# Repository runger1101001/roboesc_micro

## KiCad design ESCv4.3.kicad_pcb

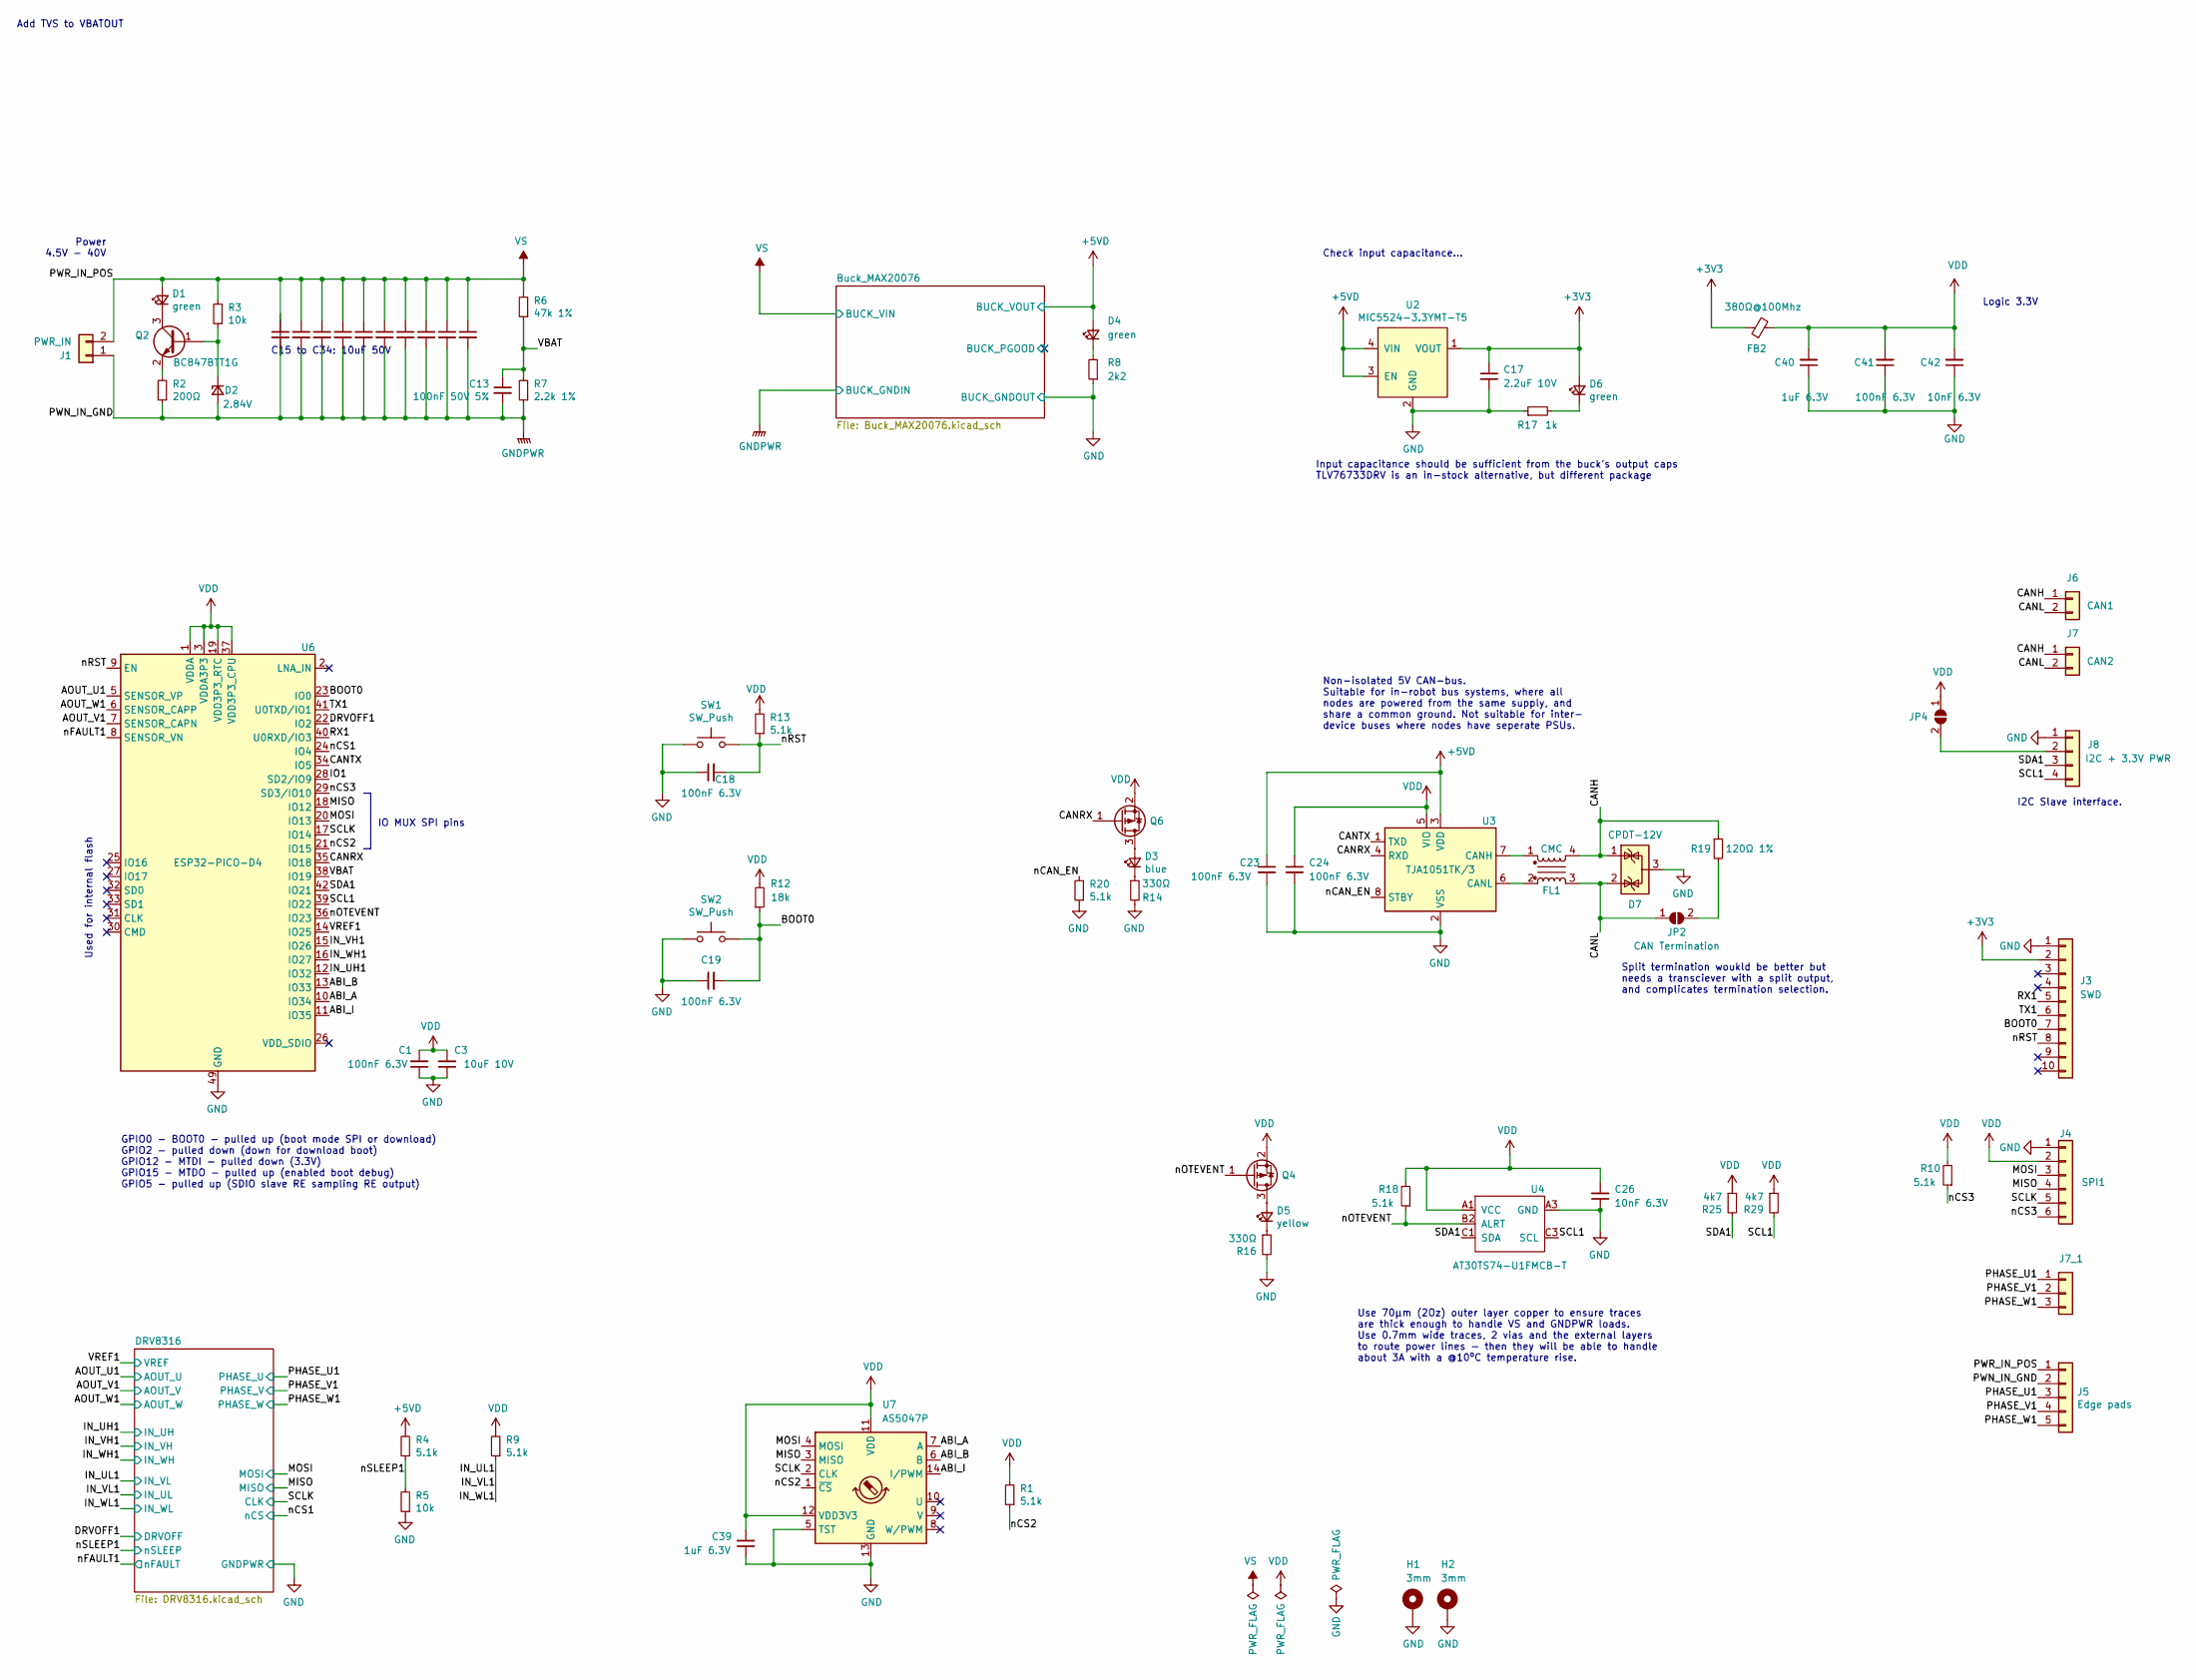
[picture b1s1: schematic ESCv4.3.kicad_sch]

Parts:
C1, C18, C19, C41: 100nF 6.3V; C_0402_1005Metric; Part CL05B104KQ5NNNC
C2, C4, C5, C6, C7, C8, C9, C10, C11, C12: 10uF 50V; C_0805_2012Metric; Part GRM21BR61H106KE43L
C3: 10uF 10V; C_0402_1005Metric; Part ZRB15XR61A106ME01D
C13: 100nF 50V 5%; C_0402_1005Metric; Part GRM155C71H104JE19D
C17: 2.2uF 10V; C_0603_1608Metric; Part GRM188R71A225KE15D
C23, C24: 100nF 6.3V; C_0402_1005Metric
C26, C42: 10nF 6.3V; C_0402_1005Metric; Part CC0402KRX7R5BB103
C39, C40: 1uF 6.3V; C_0402_1005Metric; Part GRT155C80J105KE01D
D1, D4, D6: green; LED_0402_1005Metric; Part SML-P12MTT86
D2: 2.84V; D_SOD-523; Part CZRU52C2V7-HF
D3: blue; LED_0402_1005Metric; Part LB QH9G-N1OO-35-1
D5: yellow; LED_0402_1005Metric; Part SML-P12YTT86RR
D7: CPDT-12V; SOT-23; Part CPDT-12V
FB2: 380Ω@100Mhz; L_0603_1608Metric; Part BLM18DN381SH1D
FL1: CMC; CMC_Filter_0504; Part KCZ1210AH900HRTD25
H1, H2: 3mm; MountingHole_2.2mm_M2_Pad_Via
J1: PWR_IN; AMASS_XT30UPB-M_1x02_P5.0mm_Vertical
J3: Conn_01x10; SAMTEC_SEI-110_Mating
J4: SPI1; JST_SH_BM06B-SRSS-TB_1x06-1MP_P1.00mm_Vertical; Part JST_SH_BM06B-SRSS-TB_1x06-1MP
J5: Conn_01x05; Motor_Power_Pads_CircleEdge40mm
J6: CAN1; JST_PH_B2B-PH-K_1x02_P2.00mm_Vertical; Part JST_PH_B2B-PH-K_1x02_P2.00mm_Vertical
J7: CAN2; JST_PH_B2B-PH-K_1x02_P2.00mm_Vertical; Part JST_PH_B2B-PH-K_1x02_P2.00mm_Vertical
J7_1: Phase_Pads; PinHeader_1x03_P2.54mm_Vertical
J8: Conn_01x04; JST_SH_BM04B-SRSS-TB_1x04-1MP_P1.00mm_Vertical; Part JST_SH_BM04B-SRSS-TB_1x04-1MP
JP2: CAN Termination; SolderJumper-2_P1.3mm_Open_TrianglePad1.0x1.5mm
JP4: SolderJumper_2_Open; SolderJumper-2_P1.3mm_Open_TrianglePad1.0x1.5mm
Q2: BC847BTT1G; SOT-416; Part BC847BTT1G
Q4, Q6: CSD25501F3; FemtoFET_0.7x0.6_YJN3; Part CSD25501F3
R1, R4, R9, R10, R13, R18, R20: 5.1k; R_0402_1005Metric
R2: 200Ω; R_0402_1005Metric
R3, R5: 10k; R_0402_1005Metric
R6: 47k 1%; R_0402_1005Metric
R7: 2.2k 1%; R_0402_1005Metric
R8: 2k2; R_0402_1005Metric
R12: 18k; R_0402_1005Metric
R14, R16: 330Ω; R_0402_1005Metric
R17: 1k; R_0402_1005Metric
R19: 120Ω 1%; R_0402_1005Metric
R25, R29: 4k7; R_0402_1005Metric
SW1: SW_Push; NANOT240; Part USLPT2616CT2TR
SW2: SW_Push; NANOT240; Part NANOT240
U2: MIC5524-3.3YMT-T5; TDFN-4-1EP_1x1mm_P0.65mm_EP0.5x0.5mm; Part MIC5524-3.3YMT-T5
U3: TJA1051TK/3; DFN-8-1EP_3x3mm_P0.65mm_EP1.55x2.4mm; Part TJA1051TK/3
U4: AT30TS74-U1FMCB-T; Texas_DSBGA-5_0.822x1.116mm_Layout2x1x2_P0.4mm; Part AT30TS74-U1FMCB-T
U6: ESP32-PICO-D4; QFN-48-1EP_7x7mm_P0.5mm_EP5.3x5.3mm; Part ESP32-PICO-D4
U7: AS5047P; TSSOP-14_4.4x5mm_P0.65mm; Part AS5047P

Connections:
+3V3: C17.1, D6.2 (A), FB2.1, J3.2, U2.1 (VOUT); also elsewhere on the board
+5VD: C23.1, D4.2 (A), R4.2, U2.3 (EN), U2.4 (VIN), U3.3 (VDD); also elsewhere on the board
/ABI_A: U6.10 (IO34), U7.7 (A)
/ABI_B: U6.13 (IO33), U7.6 (B)
/ABI_I: U6.11 (IO35), U7.14 (I/PWM)
/AOUT_U1: U6.5 (SENSOR_VP); also elsewhere on the board
/AOUT_V1: U6.7 (SENSOR_CAPN); also elsewhere on the board
/AOUT_W1: U6.6 (SENSOR_CAPP); also elsewhere on the board
/BOOT0: C19.2, J3.7, R12.1, SW2.2, U6.23 (IO0); also elsewhere on the board
/CANH: D7.1 (K), FL1.4, J6.1, J7.1, R19.1
/CANL: D7.2 (K), FL1.3, J6.2, J7.2, JP2.1 (A)
/CANRX: Q6.1 (G), U3.4 (RXD), U6.35 (IO18)
/CANTX: U3.1 (TXD), U6.34 (IO5)
/DRVOFF1: U6.22 (IO2); also elsewhere on the board
/IN_UH1: U6.12 (IO32); also elsewhere on the board
/IN_UL1: R9.1; also elsewhere on the board
/IN_VH1: U6.15 (IO26); also elsewhere on the board
/IN_WH1: U6.16 (IO27); also elsewhere on the board
/IO1: U6.28 (SD2/IO9)
/MISO: J4.4, U6.18 (IO12), U7.3 (MISO); also elsewhere on the board
/MOSI: J4.3, U6.20 (IO13), U7.4 (MOSI); also elsewhere on the board
/PHASE_U1: J5.3, J7_1.1; also elsewhere on the board
/PHASE_V1: J5.4, J7_1.2; also elsewhere on the board
/PHASE_W1: J5.5, J7_1.3; also elsewhere on the board
/RX1: J3.5, U6.40 (U0RXD/IO3); also elsewhere on the board
/SCL1: J8.4, R29.2, U4.C3 (SCL), U6.39 (IO22)
/SCLK: J4.5, U6.17 (IO14), U7.2 (CLK); also elsewhere on the board
/SDA1: J8.3, R25.2, U4.C1 (SDA), U6.42 (IO21)
/TX1: J3.6, U6.41 (U0TXD/IO1); also elsewhere on the board
/VBAT: C13.1, R6.1, R7.2, U6.38 (IO19)
/VREF1: U6.14 (IO25); also elsewhere on the board
/nCAN_EN: R20.2, U3.8 (STBY)
/nCS1: U6.24 (IO4); also elsewhere on the board
/nCS2: R1.1, U6.21 (IO15), U7.1 (~CS)
/nCS3: J4.6, R10.1, U6.29 (SD3/IO10)
/nFAULT1: U6.8 (SENSOR_VN); also elsewhere on the board
/nOTEVENT: Q4.1 (G), R18.1, U4.B2 (ALRT), U6.36 (IO23)
/nRST: C18.2, J3.8, R13.1, SW1.2, U6.9 (EN); also elsewhere on the board
/nSLEEP1: R4.1, R5.2; also elsewhere on the board
unnamed: D1.1 (K), Q2.3 (C)
unnamed: D2.1 (K), Q2.1 (B), R3.1
unnamed: D3.1 (K), R14.1
unnamed: D3.2 (A), Q6.3 (D)
unnamed: D4.1 (K), R8.2
unnamed: D5.1 (K), R16.1
unnamed: D5.2 (A), Q4.3 (D)
unnamed: D6.1 (K), R17.2
unnamed: FL1.1, U3.7 (CANH)
unnamed: FL1.2, U3.6 (CANL)
unnamed: J8.2, JP4.2 (B)
unnamed: JP2.2 (B), R19.2
unnamed: Q2.2 (E), R2.2
VS: C2.1, C4.1, C5.1, C6.1, C7.1, C8.1, C9.1, C10.1, C11.1, C12.1, D1.2 (A), J1.2, J5.1, R3.2, R6.2; also elsewhere on the board

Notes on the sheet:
Add TVS to VBATOUT
IO MUX SPI pins
Input capacitance should be sufficient from the buck’s output caps TLV76733DRV is an in-stock alternative, but different package
I2C Slave interface.
GPIO0 - BOOT0 - pulled up (boot mode SPI or download) GPIO2 - pulled down (down for download boot) GPIO12 - MTDI - pulled down (3.3V) GPIO15 - MTDO - pulled up (enabled boot debug) GPIO5 - pulled up (SDIO slave RE sampling RE output)
C15 to C34: 10uF 50V
Power 4.5V - 40V
Used for internal flash
Logic 3.3V
Check input capacitance…
Non-isolated 5V CAN-bus. Suitable for in-robot bus systems, where all nodes are powered from the same supply, and share a common ground. Not suitable for inter- device buses where nodes have seperate PSUs.
Split termination woukld be better but needs a transciever with a split output, and complicates termination selection.
Use 70µm (2Oz) outer layer copper to ensure traces are thick enough to handle VS and GNDPWR loads. Use 0.7mm wide traces, 2 vias and the external layers to route power lines - then they will be able to handle about 3A with a @10ºC temperature rise.

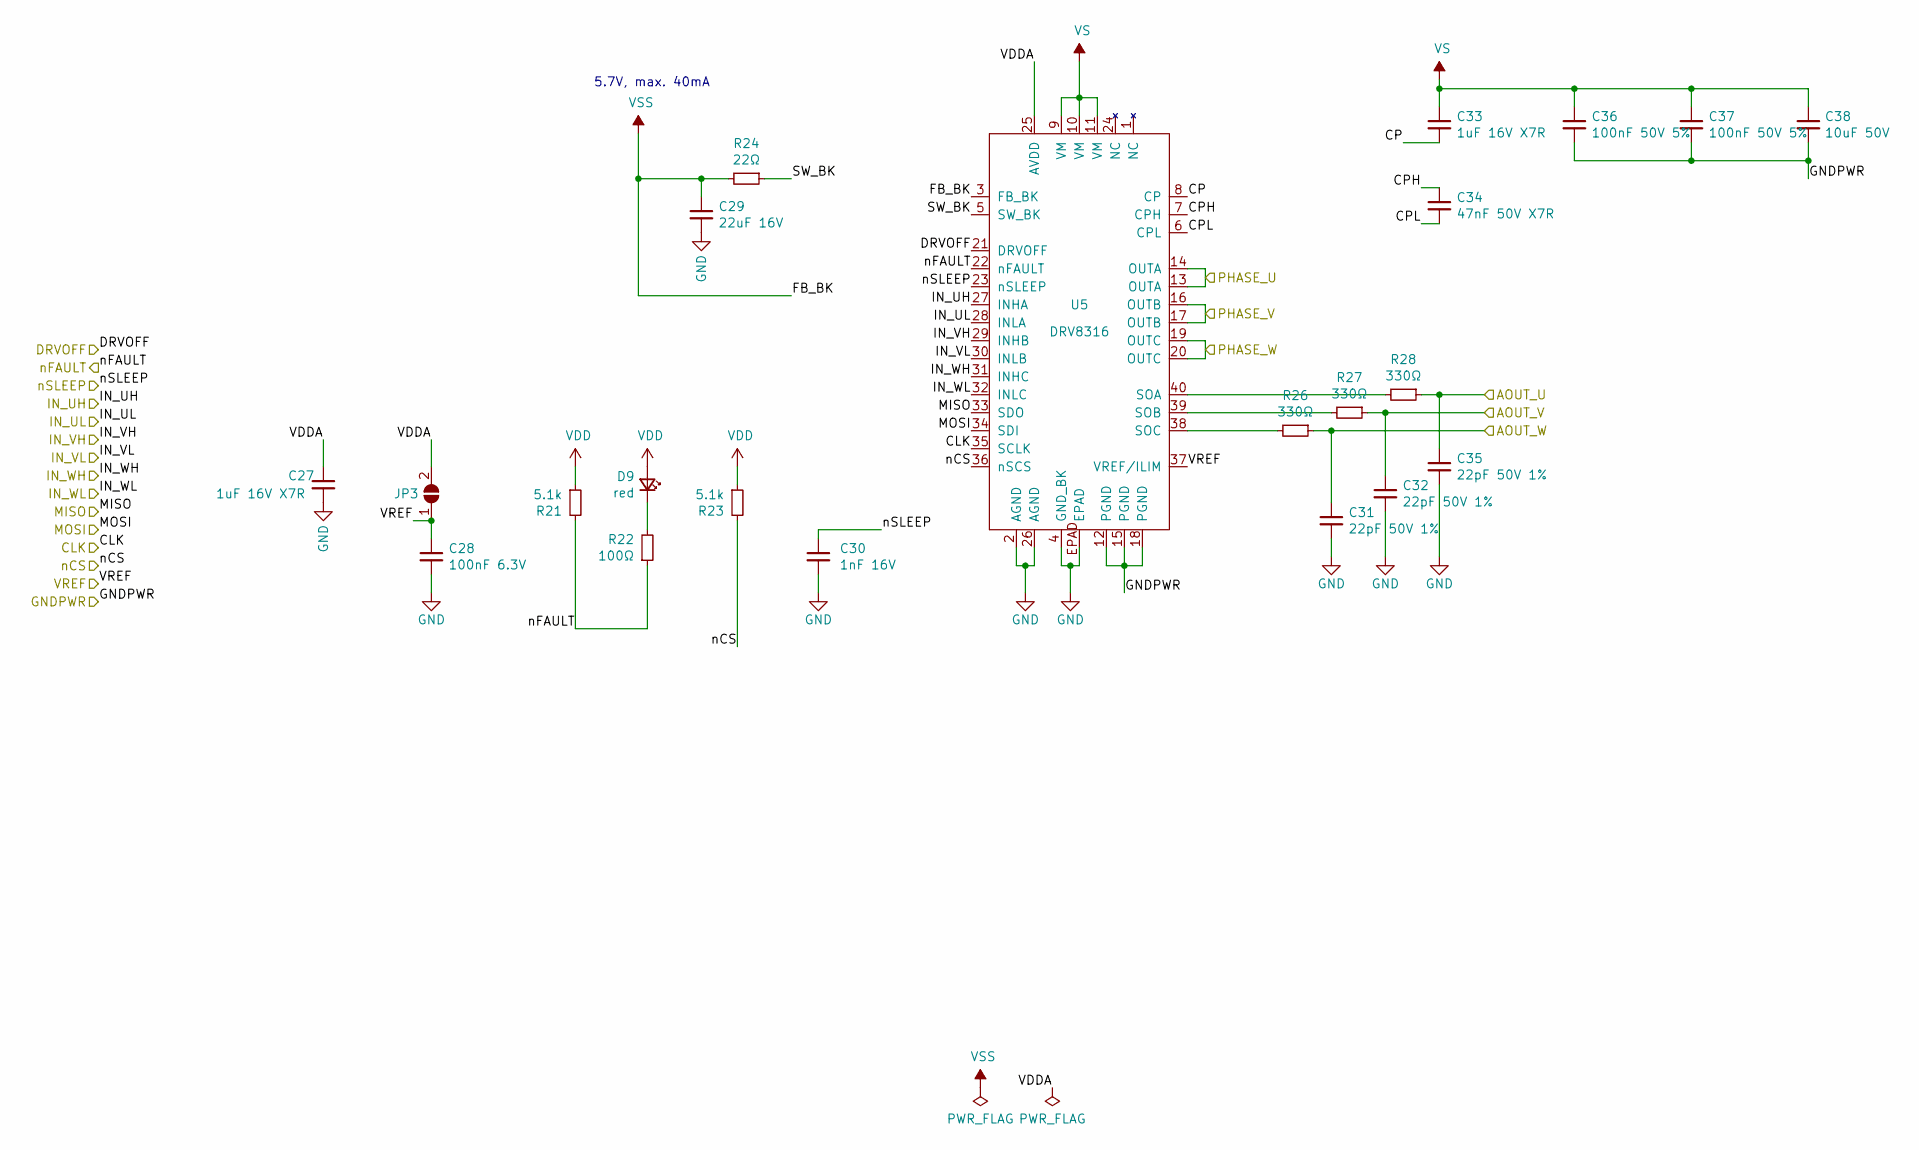
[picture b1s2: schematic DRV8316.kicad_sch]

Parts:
C27: 1uF 16V X7R; C_0402_1005Metric; Part 0603YC105JAT2A
C28: 100nF 6.3V; C_0402_1005Metric; Part CL05B104KQ5NNNC
C29: 22uF 16V; C_0805_2012Metric; Part GRM219R61C226ME15L
C30: 1nF 16V; C_0402_1005Metric; Part 0402YC102KAT2A
C31, C32, C35: 22pF 50V 1%; C_0402_1005Metric; Part GRM1555C1H220FA01D
C33: 1uF 16V X7R; C_0603_1608Metric; Part 0603YC105JAT2A
C34: 47nF 50V X7R; C_0402_1005Metric; Part GRM155R71H473KE14D
C36, C37: 100nF 50V 5%; C_0402_1005Metric; Part GRM155C71H104JE19D
C38: 10uF 50V; C_0805_2012Metric; Part GRM21BR61H106KE43L
D9: red; LED_0402_1005Metric; Part 150040RS73240
JP3: VSS2VDD; SolderJumper-2_P1.3mm_Open_TrianglePad1.0x1.5mm
R21, R23: 5.1k; R_0402_1005Metric
R22: 100Ω; R_0402_1005Metric
R24: 22Ω; R_0402_1005Metric
R26, R27, R28: 330Ω; R_0402_1005Metric
U5: DRV8316; vQFN-40_EP_5x7_Pitch0.5mm; Part DRV8316

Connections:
/AOUT_U1: C35.1, R28.1; also elsewhere on the board
/AOUT_V1: C32.1, R27.1; also elsewhere on the board
/AOUT_W1: C31.1, R26.1; also elsewhere on the board
/DRV8316/CP: C33.2, U5.8 (CP)
/DRV8316/CPH: C34.1, U5.7 (CPH)
/DRV8316/CPL: C34.2, U5.6 (CPL)
/DRV8316/SW_BK: R24.1, U5.5 (SW_BK)
/DRV8316/VDDA: C27.1, JP3.2 (B), U5.25 (AVDD)
/DRVOFF1: U5.21 (DRVOFF); also elsewhere on the board
/IN_UH1: U5.27 (INHA); also elsewhere on the board
/IN_UL1: U5.28 (INLA), U5.30 (INLB), U5.32 (INLC); also elsewhere on the board
/IN_VH1: U5.29 (INHB); also elsewhere on the board
/IN_WH1: U5.31 (INHC); also elsewhere on the board
/MISO: U5.33 (SDO); also elsewhere on the board
/MOSI: U5.34 (SDI); also elsewhere on the board
/PHASE_U1: U5.13 (OUTA), U5.14 (OUTA); also elsewhere on the board
/PHASE_V1: U5.16 (OUTB), U5.17 (OUTB); also elsewhere on the board
/PHASE_W1: U5.19 (OUTC), U5.20 (OUTC); also elsewhere on the board
/SCLK: U5.35 (SCLK); also elsewhere on the board
/VREF1: C28.1, JP3.1 (A), U5.37 (VREF/ILIM); also elsewhere on the board
/nCS1: R23.2, U5.36 (nSCS); also elsewhere on the board
/nFAULT1: R21.2, R22.1, U5.22 (nFAULT); also elsewhere on the board
/nSLEEP1: C30.1, U5.23 (nSLEEP); also elsewhere on the board
unnamed: D9.1 (K), R22.2
unnamed: R26.2, U5.38 (SOC)
unnamed: R27.2, U5.39 (SOB)
unnamed: R28.2, U5.40 (SOA)
VS: C33.1, C36.1, C37.1, C38.1, U5.9 (VM), U5.10 (VM), U5.11 (VM); also elsewhere on the board
VSS: C29.1, R24.2, U5.3 (FB_BK)

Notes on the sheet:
5.7V, max. 40mA

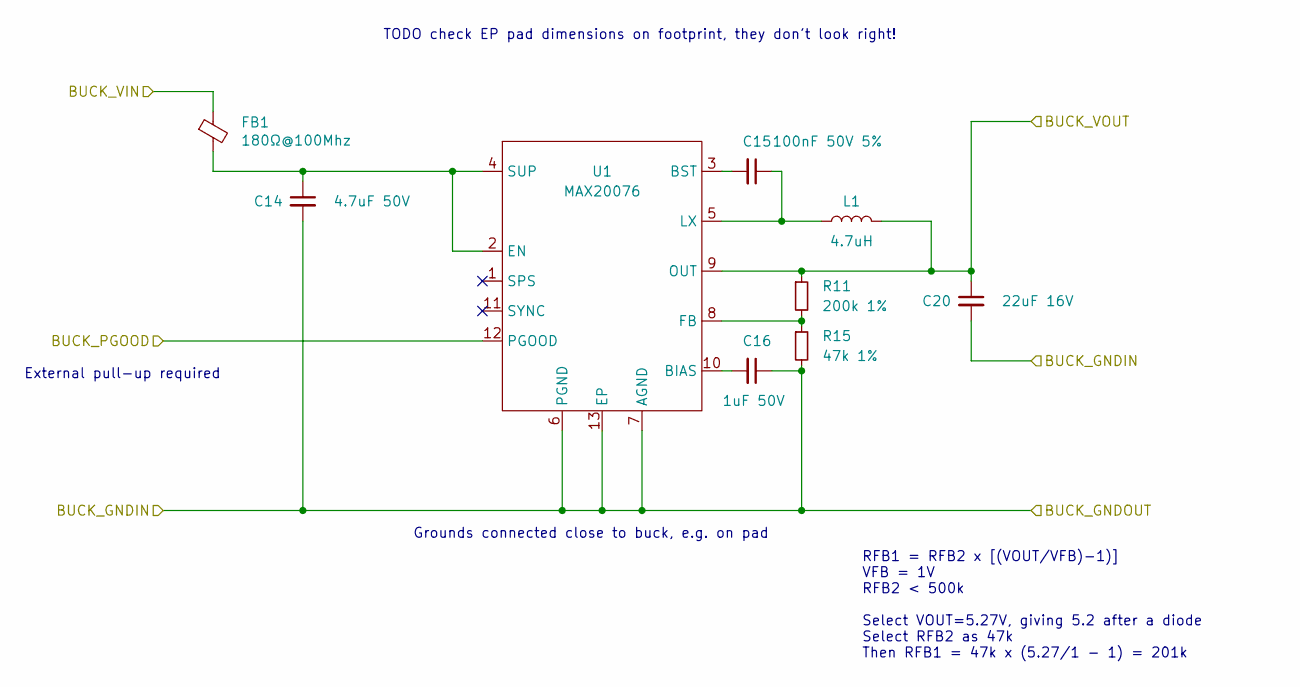
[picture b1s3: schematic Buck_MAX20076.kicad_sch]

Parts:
C14: 4.7uF 50V; C_0805_2012Metric; Part GRM21BZ71H475ME15K
C15: 100nF 50V 5%; C_0402_1005Metric; Part GRM155C71H104JE19D
C16: 1uF 50V; C_0402_1005Metric; Part GRM155R61H105KE05D
C20: 22uF 16V; C_0603_1608Metric; Part CL10A226MO7JZNC
FB1: 180Ω@100Mhz; L_0805_2012Metric; Part BLM21SP181SZ1D
L1: 4.7uH; L_Coilcraft_XxL4030; Part XAL4030-472MEC
R11: 200k 1%; R_0402_1005Metric; Part ERJ2RKD2003X
R15: 47k 1%; R_0402_1005Metric; Part TNPW040247K0BYEP
U1: MAX20076; DFN-12-1EP_3x3mm_P0.5mm_EP1.7x2.5mm; Part MAX20076EATCB/VY+

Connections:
+5VD: C20.1, L1.2, R11.1, U1.9 (OUT); also elsewhere on the board
/Buck_MAX20076/BUCK_PGOOD: U1.12 (PGOOD)
unnamed: C14.1, FB1.2, U1.2 (EN), U1.4 (SUP)
unnamed: C15.1, L1.1, U1.5 (LX)
unnamed: C15.2, U1.3 (BST)
unnamed: C16.2, U1.10 (BIAS)
unnamed: R11.2, R15.1, U1.8 (FB)
VS: FB1.1; also elsewhere on the board

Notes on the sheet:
TODO check EP pad dimensions on footprint, they don't look right!
Grounds connected close to buck, e.g. on pad
RFB1 = RFB2 x [(VOUT/VFB)-1)] VFB = 1V RFB2 < 500k Select VOUT=5.27V, giving 5.2 after a diode Select RFB2 as 47k Then RFB1 = 47k x (5.27/1 - 1) = 201k
External pull-up required

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
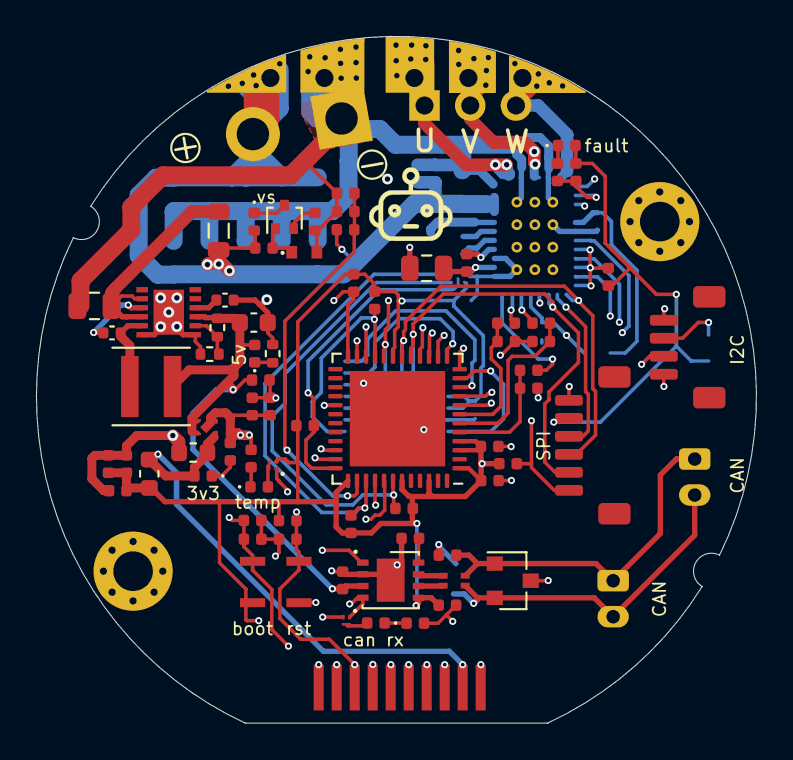
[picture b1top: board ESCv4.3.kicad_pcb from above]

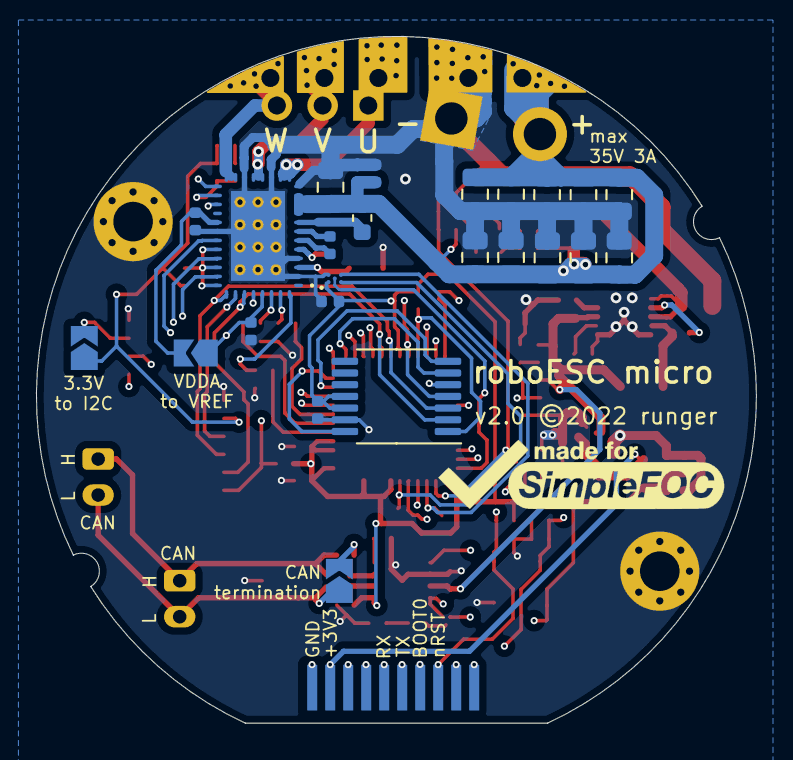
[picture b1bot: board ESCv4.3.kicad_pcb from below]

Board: 4 copper layers, 40.0 x 38.1 mm, 106 parts (26 on the bottom side), 69 nets.

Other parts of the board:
J3#2: Conn_01x10; SAMTEC_SEI-110_Mating

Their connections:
+3V3: J3#2.2; also elsewhere on the board
/BOOT0: J3#2.7; also elsewhere on the board
/RX1: J3#2.5; also elsewhere on the board
/TX1: J3#2.6; also elsewhere on the board
/nRST: J3#2.8; also elsewhere on the board

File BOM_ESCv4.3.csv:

Item,Ref Des,Qty,Manufacturer,Mfg Part #,Description / Value,Package,Type,Your Instructions / Notes
1,"C13,C16,C36,C37",4,Murata,GRM155C71H104JE19D,100nF 50V 5%,C_0402_1005Metric,SMD,GRM155C71H104JE19D or similar; Unpolarized capacitor;
2,C17,1,Murata,GRM188R71A225KE15D,2.2uF 10V,C_0603_1608Metric,SMD,; Unpolarized capacitor; 
3,"C18,C19,C23,C24,C41,C1,C28",7,Samsung,CL05B104KQ5NNNC,100nF 6.3V,C_0402_1005Metric,SMD,CL05B104KQ5NNNC or similar; Unpolarized capacitor;
4,"C21,C20,C22,C29",4,Murata,GRM219R61C226ME15L,22uF 16V,C_0805_2012Metric,SMD,; Unpolarized capacitor; 
5,"C26,C42",2,Yageo,CC0402KRX7R5BB103,10nF 6.3V,C_0402_1005Metric,SMD,Any 10nF 6.3V X5R or X7R ceramic capacitor; Unpolarized capacitor;
6,C3,1,Murata,ZRB15XR61A106ME01D,10uF 10V,C_0402_1005Metric,SMD,; Unpolarized capacitor; 
7,C30,1,AVX,0402YC102KAT2A,1nF 16V,C_0402_1005Metric,SMD,0402YC102KAT2A or similar 1nF 16V; Unpolarized capacitor;
8,"C31,C32,C35",3,Murata,GRM1555C1H220FA01D,22pF 50V 1%,C_0402_1005Metric,SMD,GRM1555C1H220FA01D - 50V.    ; Unpolarized capacitor;
9,"C33,C27",2,AVX,0603YC105JAT2A,1uF 16V X7R,C_0402_1005Metric,SMD,6.3V would be enough; Unpolarized capacitor;
10,C34,1,Murata,GRM155R71H473KE14D,47nF 50V X7R,C_0402_1005Metric,SMD,; Unpolarized capacitor; 
11,"C39,C40",2,Murata,GRT155C80J105KE01D,1uF 6.3V,C_0402_1005Metric,SMD,; Unpolarized capacitor; 
12,"C4,C2,C6,C5,C7,C9,C8,C10,C12,C11,C14,C15,C38",13,Murata,GRM21BR61H106KE43L,10uF 50V,C_0805_2012Metric,SMD,; Unpolarized capacitor; 
13,"D1,D4,D6",3,ROHM,SML-P12MTT86,green,LED_0402_1005Metric,SMD,; Light emitting diode; 
14,D2,1,Comchip,CZRU52C2V7-HF,2.84V,D_SOD-523,SMD,Any 2.84V (+/-0.2V) Zener diode; Zener diode; https://www.mouser.at/datasheet/2/80/CZRU52C2-HF_THRU_CZRU52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
15,D3,1,OSRAM Opto,LB QH9G-N1OO-35-1,blue,LED_0402_1005Metric,SMD,; Light emitting diode; 
16,D5,1,ROHM Semiconductors,SML-P12YTT86RR,yellow,LED_0402_1005Metric,SMD,; Light emitting diode; 
17,D7,1,Comchip,CPDT-12V,CPDT-12V,SOT-23,SMD,"; Dual Line CAN Bus Protector, 24Vrwm; http://www.onsemi.com/pub_link/Collateral/NUP2105L-D.PDF"
18,D9,1,Wurth,150040RS73240,red,LED_0402_1005Metric,SMD,any approx. 2V red LED; Light emitting diode; https://www.mouser.at/datasheet/2/445/150040RS73240-1713960.pdf
19,FB1,1,Murata,BLM21SP181SZ1D,180Ω@100Mhz,L_0805_2012Metric,SMD,; Ferrite bead; 
20,FB2,1,Murata,BLM18DN381SH1D,380Ω@100Mhz,L_0603_1608Metric,SMD,; Ferrite bead; 
21,FL1,1,TDK,KCZ1210AH900HRTD25,CMC,CMC_Filter_0504,SMD,"; EMI 2-inductor filter, pin-connections 1-4 and 2-3;"
25,J4,1,JST,JST_SH_BM06B-SRSS-TB_1x06-1MP,SPI1,JST_SH_BM06B-SRSS-TB_1x06-1MP_P1.00mm_Vertical,SMD,"; Generic connector, single row, 01x06, script generated (kicad-library-utils/schlib/autogen/connector/);"
30,J8,1,JST,JST_SH_BM04B-SRSS-TB_1x04-1MP,Conn_01x04,JST_SH_BM04B-SRSS-TB_1x04-1MP_P1.00mm_Vertical,SMD,"; Generic connector, single row, 01x04, script generated (kicad-library-utils/schlib/autogen/connector/);"
34,L1,1,Coilcraft,XGL4020-102MEC,1uH,L_Coilcraft_XxL4020,SMD,; Inductor; 
35,Q2,1,On Semi,BC847BTT1G,BC847BTT1G,SOT-416,SMD,"beta=150 footprint SC-75-3; NPN transistor, base/emitter/collector;"
36,"Q4,Q6",2,TI,CSD25501F3,CSD25501F3,FemtoFET_0.7x0.6_YJN3,SMD,"; P-MOSFET transistor, gate/source/drain; "
37,R11,1,,Resistor,1MΩ,R_0402_1005Metric,SMD,; Resistor; 
38,R12,1,,Resistor,18k,R_0402_1005Metric,SMD,; Resistor; 
39,R15,1,,Resistor,2k2,R_0402_1005Metric,SMD,; Resistor; 
40,"R16,R14,R28,R27,R26",5,,Resistor,330Ω,R_0402_1005Metric,SMD,; Resistor; 
41,R17,1,,Resistor,1k,R_0402_1005Metric,SMD,; Resistor; 
42,R19,1,,Resistor,120Ω 1%,R_0402_1005Metric,SMD,; Resistor; 
43,R2,1,,Resistor,200Ω,R_0402_1005Metric,SMD,; Resistor; 
44,R22,1,,Resistor,100Ω,R_0402_1005Metric,SMD,; Resistor; 
45,R24,1,,Resistor,22Ω,R_0402_1005Metric,SMD,; Resistor; 
46,"R25,R29",2,,Resistor,4k7,R_0402_1005Metric,SMD,; Resistor; 
47,"R3,R5",2,,Resistor,10k,R_0402_1005Metric,SMD,; Resistor; 
48,"R4,R13,R18,R20,R9,R1,R10,R21,R23",9,,Resistor,5.1k,R_0402_1005Metric,SMD,; Resistor; 
49,R6,1,,Resistor,47k 1%,R_0402_1005Metric,SMD,; Resistor; 
50,R7,1,,Resistor,2.2k 1%,R_0402_1005Metric,SMD,; Resistor; 
51,"SW1,SW2",2,TE Connectivity / Alcoswitch,USLPT2616CT2TR,SW_Push,USLPT2616CT2TR,SMD,"; Push button switch, generic, two pins; "
52,U1,1,TI,TPS63061,TPS63061,Texas_S-PWSON-N10_ThermalVias,SMD,"; Buck/boost regulator 1.3A boost, 2A buck, 5V fixed output voltage; http://www.ti.com/lit/ds/symlink/tps63060.pdf"
53,U2,1,Micrel / Microchip,MIC5524-3.3YMT-T5,MIC5524-3.3YMT-T5,TDFN-4-1EP_1x1mm_P0.65mm_EP0.5x0.5mm,SMD,"; 500mA low dropout LDO, Fixed or Adjustable, 1x1mm Thin-DFN; https://www.mouser.at/datasheet/2/268/MIC5524-875860.pdf"
54,U3,1,Microchip,MCP2542WFDxMF,MCP2542WFDxMF,DFN-8-1EP_3x3mm_P0.65mm_EP1.55x2.4mm,SMD,"; CAN-FD Transceiver, Wake-Up on CAN activity, 8Mbps, 5V supply, STBY pin, 3x3 DFN-8; http://ww1.microchip.com/downloads/en/DeviceDoc/MCP2542FD-4F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"
55,U4,1,Microchip,AT30TS74-U1FMCB-T,AT30TS74-U1FMCB-T,Texas_DSBGA-5_0.822x1.116mm_Layout2x1x2_P0.4mm,SMD,"; 9- to 12-bit Selectable, ±1.0°C Accurate Digital Temperature Sensor;"
56,U5,1,Texas Instruments,DRV8316,DRV8316,vQFN-40_EP_5x7_Pitch0.5mm,SMD,; 40-V max 8-A peak 3-phase motor driver with integrated current sensing; https://www.ti.com/lit/gpn/DRV8316
57,U6,1,Espressif,ESP32-PICO-D4,ESP32-PICO-D4,QFN-48-1EP_7x7mm_P0.5mm_EP5.3x5.3mm,SMD,"; RF Module, ESP32 SoC, Wi-Fi 802.11b/g/n, Bluetooth, BLE, 32-bit, 2.7-3.6V, external antenna, QFN-48; https://www.espressif.com/sites/default/files/documentation/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"
58,U7,1,MagAlpha,MA732GQ,MA732,QFN-16-1EP_3x3mm_P0.5mm_EP1.75x1.75mm,SMD,"; Magnetic rotary angle sensor, 14-bit, SPI interface, ABZ, PWM, QFN-16; https://www.monolithicpower.com/pub/media/document/m/a/ma730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"

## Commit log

2021-10-22 gitignores
2022-04-19 production version v1
2022-04-19 add schematics PDF

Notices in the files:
ESCv4.3.kicad_pcb:
v2.0 ©2022 runger
